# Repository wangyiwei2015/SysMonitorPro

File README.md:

# SysMonitor Pro 2.0

A hardware dashboard for your computer.

### Get started

1. Connect your device to a USB port
2. Launch the application and select its COM/Serial port
3. Done!

\* *To find the serial port on Windows, go to Device Manager.*

### Build

-> build_.bat

### To-do

The Python client will be replaced by:

- Windows: .NET app
- macOS: SwiftUI app

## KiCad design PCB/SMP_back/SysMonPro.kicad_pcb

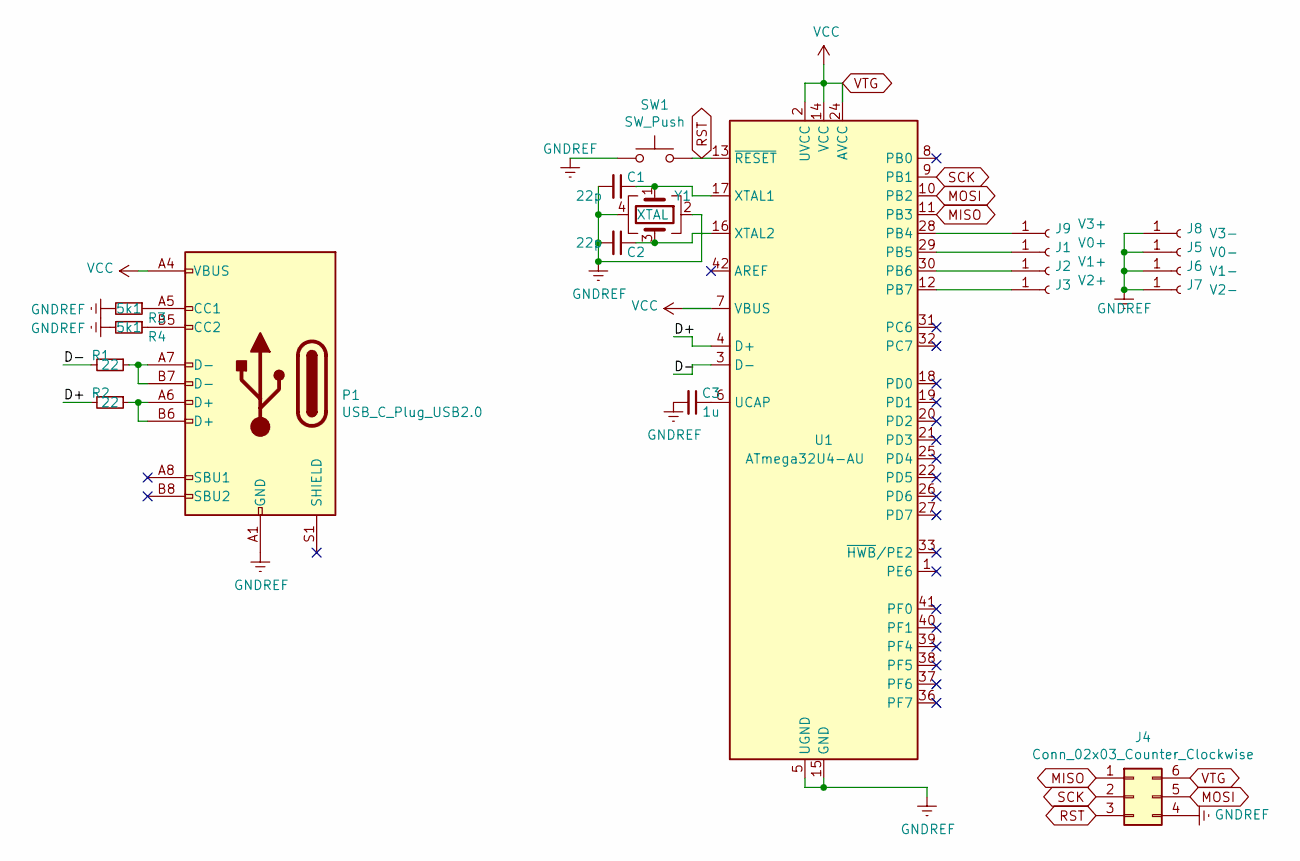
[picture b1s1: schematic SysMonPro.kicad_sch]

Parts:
C1, C2: 22p; C_0805_2012Metric_Pad1.18x1.45mm_HandSolder
C3: 1u; C_0805_2012Metric_Pad1.18x1.45mm_HandSolder
J1: V0+; MountingHole_4.3mm_M4_Pad_Via
J2: V1+; MountingHole_4.3mm_M4_Pad_Via
J3: V2+; MountingHole_4.3mm_M4_Pad_Via
J4: Conn_02x03_Counter_Clockwise; PinSocket_2x03_P2.54mm_Vertical
J5: V0-; MountingHole_4.3mm_M4_Pad_Via
J6: V1-; MountingHole_4.3mm_M4_Pad_Via
J7: V2-; MountingHole_4.3mm_M4_Pad_Via
J8: V3-; MountingHole_4.3mm_M4_Pad_Via
J9: V3+; MountingHole_4.3mm_M4_Pad_Via
P1: USB_C_Plug_USB2.0; USB_C_Receptacle_Palconn_UTC16-G
R1, R2: 22; R_0805_2012Metric_Pad1.20x1.40mm_HandSolder
R3, R4: 5k1; R_0805_2012Metric_Pad1.20x1.40mm_HandSolder
SW1: SW_Push; SW_SPST_SKQG_WithStem
U1: ATmega32U4-AU; TQFP-44_10x10mm_P0.8mm
Y1: XTAL; Crystal_SMD_3225-4Pin_3.2x2.5mm_HandSoldering

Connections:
/D+: R2.2, U1.4 (D+)
/D-: R1.2, U1.3 (D-)
GNDREF: C1.2, C2.2, C3.2, J4.4, J5.1, J6.1, J7.1, J8.1, P1.A1 (GND), P1.A12 (GND), P1.B1 (GND), P1.B12 (GND), R3.2, R4.2, SW1.1, U1.5 (UGND), U1.15 (GND), U1.23 (GND), U1.35 (GND), U1.43 (GND), Y1.2, Y1.4
MISO: J4.1, U1.11 (PB3)
MOSI: J4.5, U1.10 (PB2)
unnamed: C1.1, U1.17 (XTAL1), Y1.1
unnamed: C2.1, U1.16 (XTAL2), Y1.3
unnamed: C3.1, U1.6 (UCAP)
unnamed: J1.1, U1.29 (PB5)
unnamed: J2.1, U1.30 (PB6)
unnamed: J3.1, U1.12 (PB7)
unnamed: J9.1, U1.28 (PB4)
unnamed: P1.A5 (CC1), R3.1
unnamed: P1.A6 (D+), P1.B6 (D+), R2.1
unnamed: P1.A7 (D-), P1.B7 (D-), R1.1
unnamed: P1.B5 (CC2), R4.1
RST: J4.3, SW1.2, U1.13 (~RESET)
SCK: J4.2, U1.9 (PB1)
VTG: J4.6, P1.A4 (VBUS), P1.A9 (VBUS), P1.B4 (VBUS), P1.B9 (VBUS), U1.2 (UVCC), U1.7 (VBUS), U1.14 (VCC), U1.24 (AVCC), U1.34 (VCC), U1.44 (AVCC)

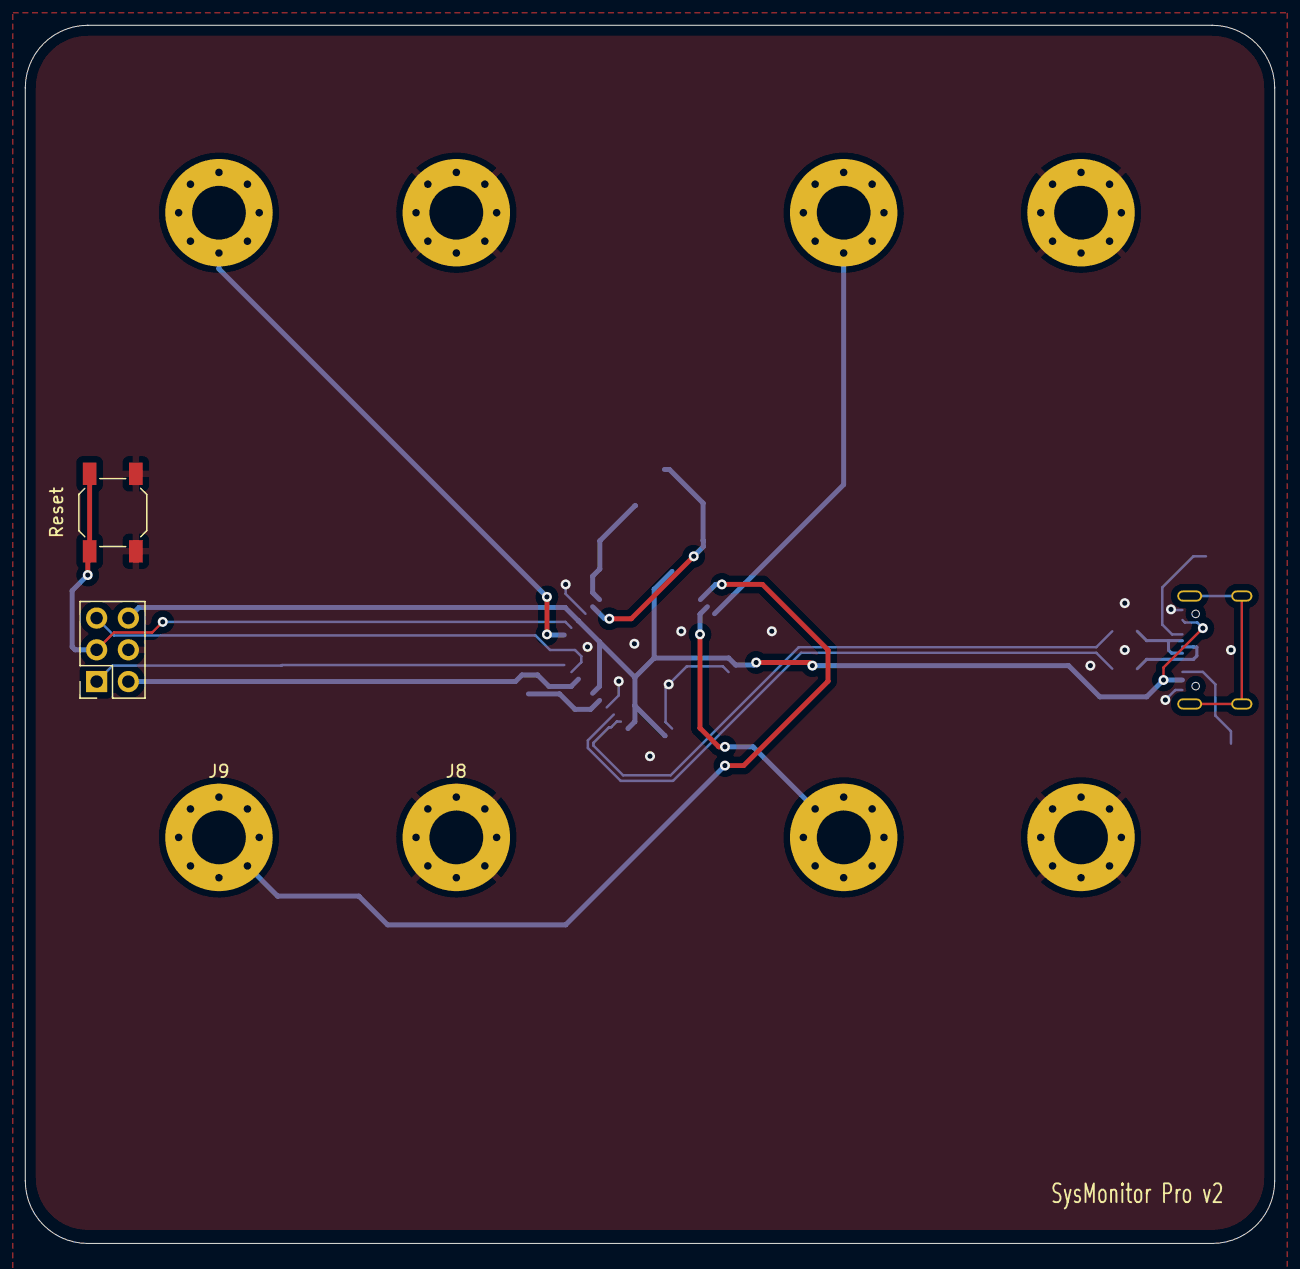
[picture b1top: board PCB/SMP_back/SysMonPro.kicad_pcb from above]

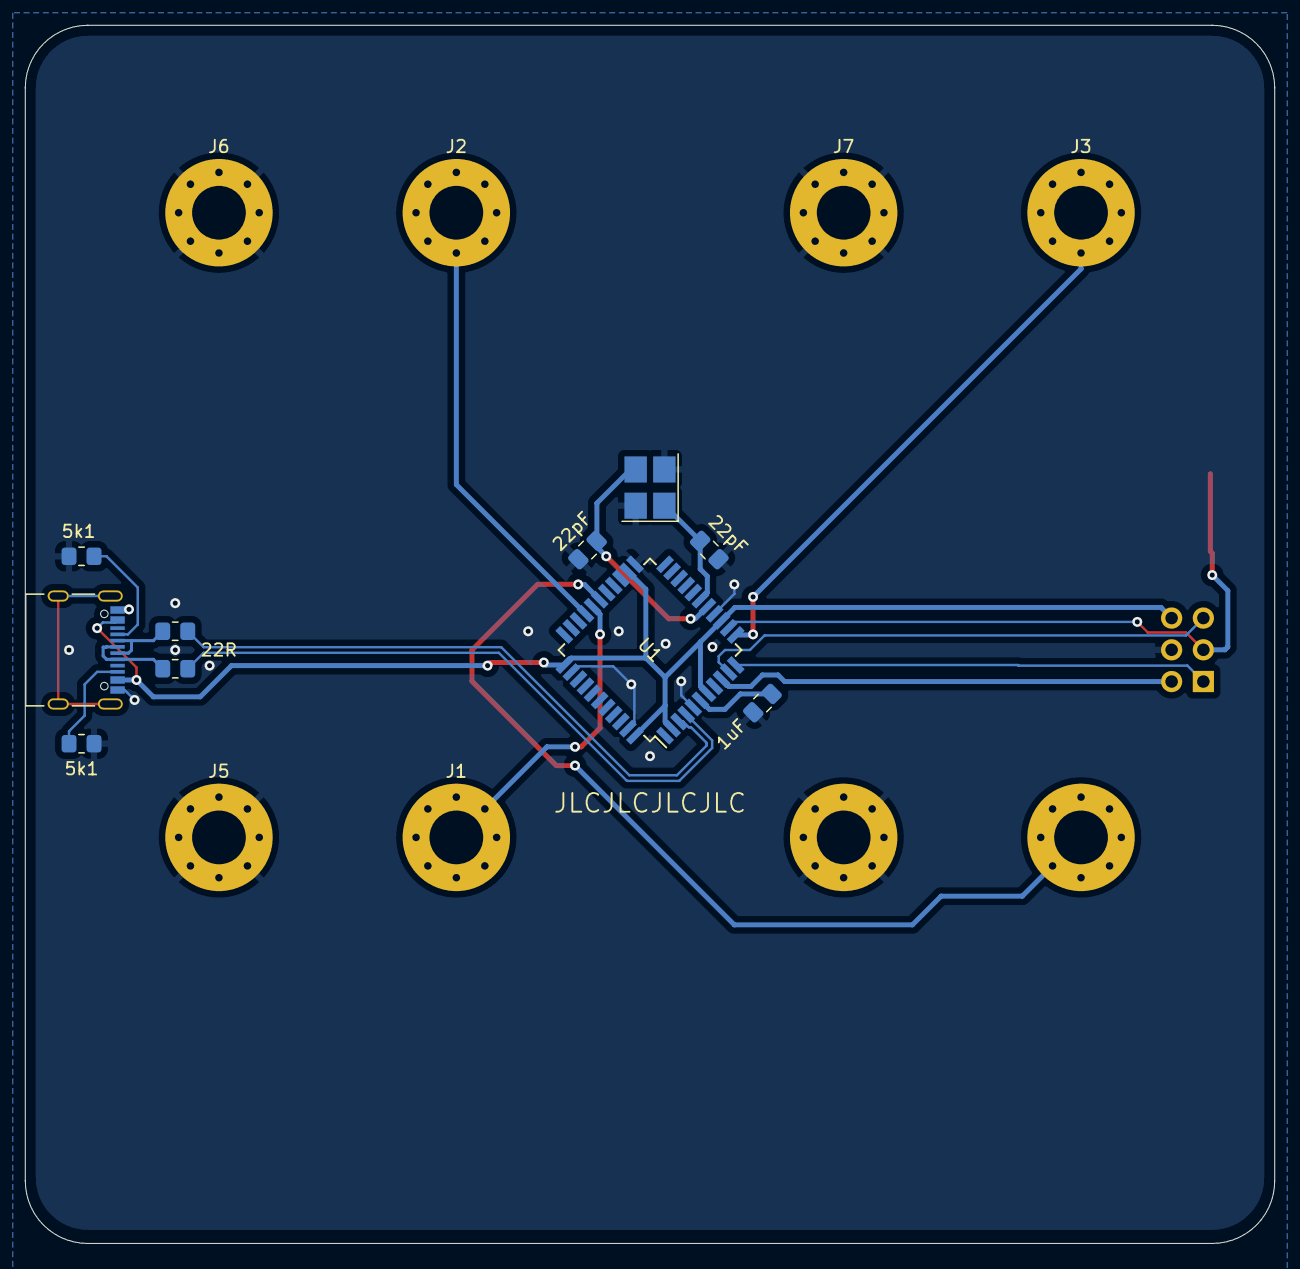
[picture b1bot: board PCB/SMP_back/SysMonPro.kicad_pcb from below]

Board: 2 copper layers, 100.0 x 97.5 mm, 20 parts (16 on the bottom side), 19 nets.

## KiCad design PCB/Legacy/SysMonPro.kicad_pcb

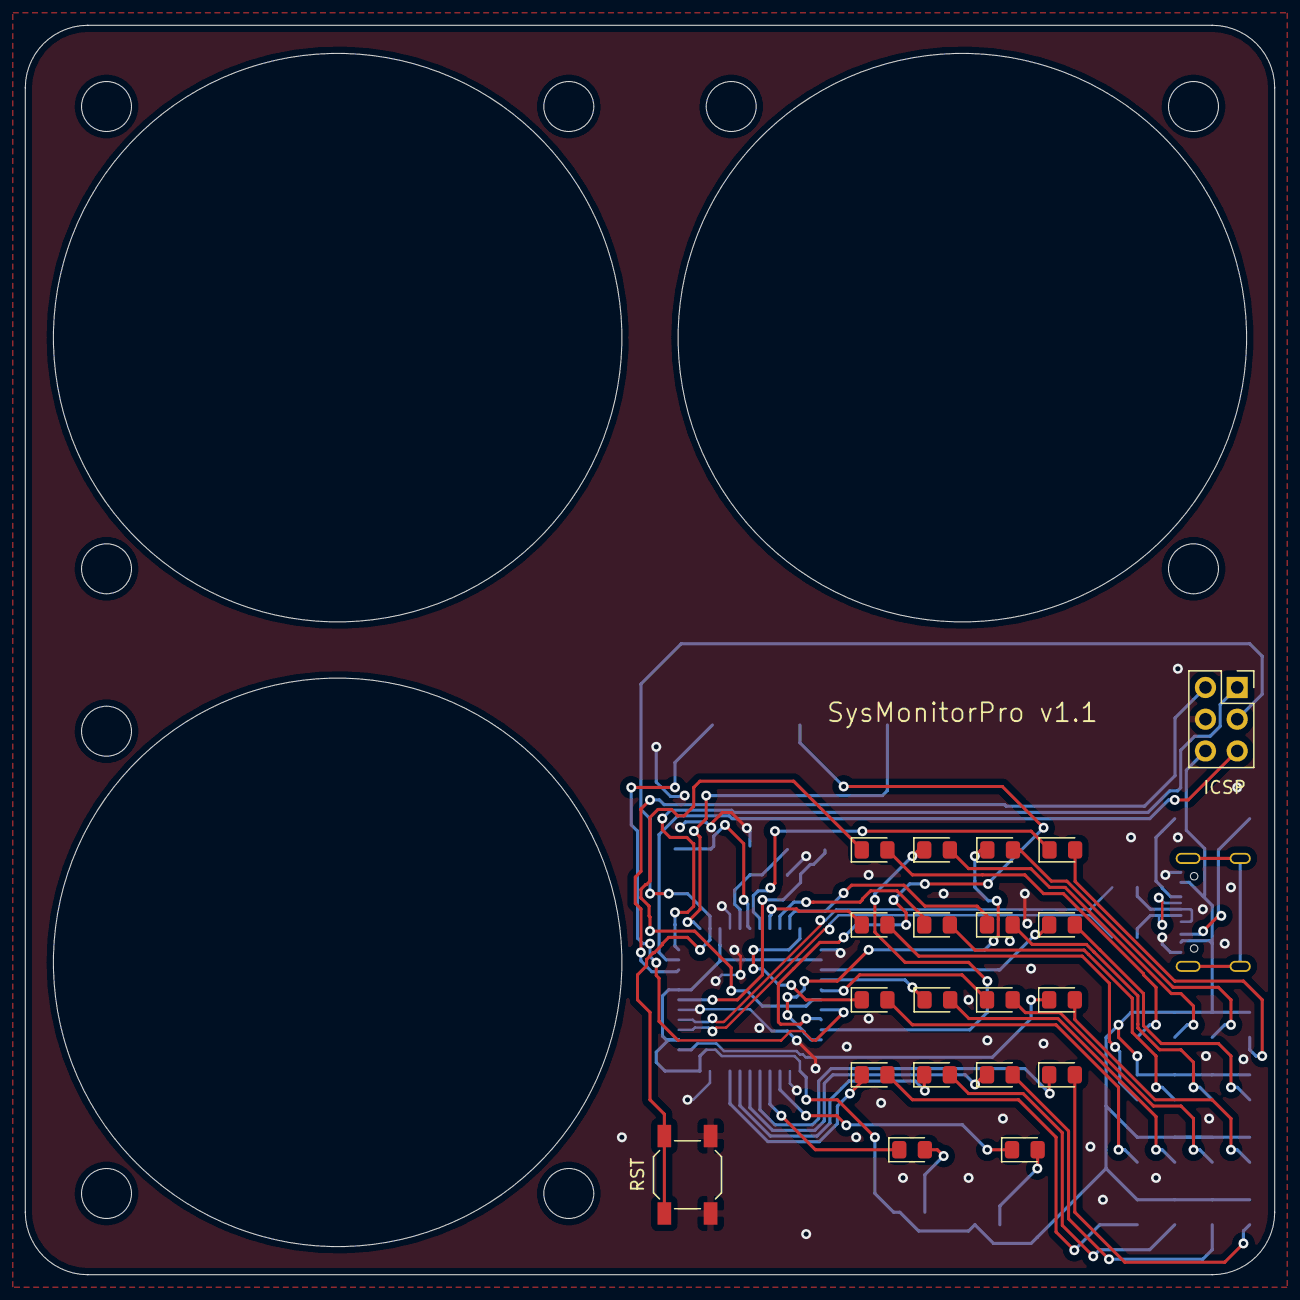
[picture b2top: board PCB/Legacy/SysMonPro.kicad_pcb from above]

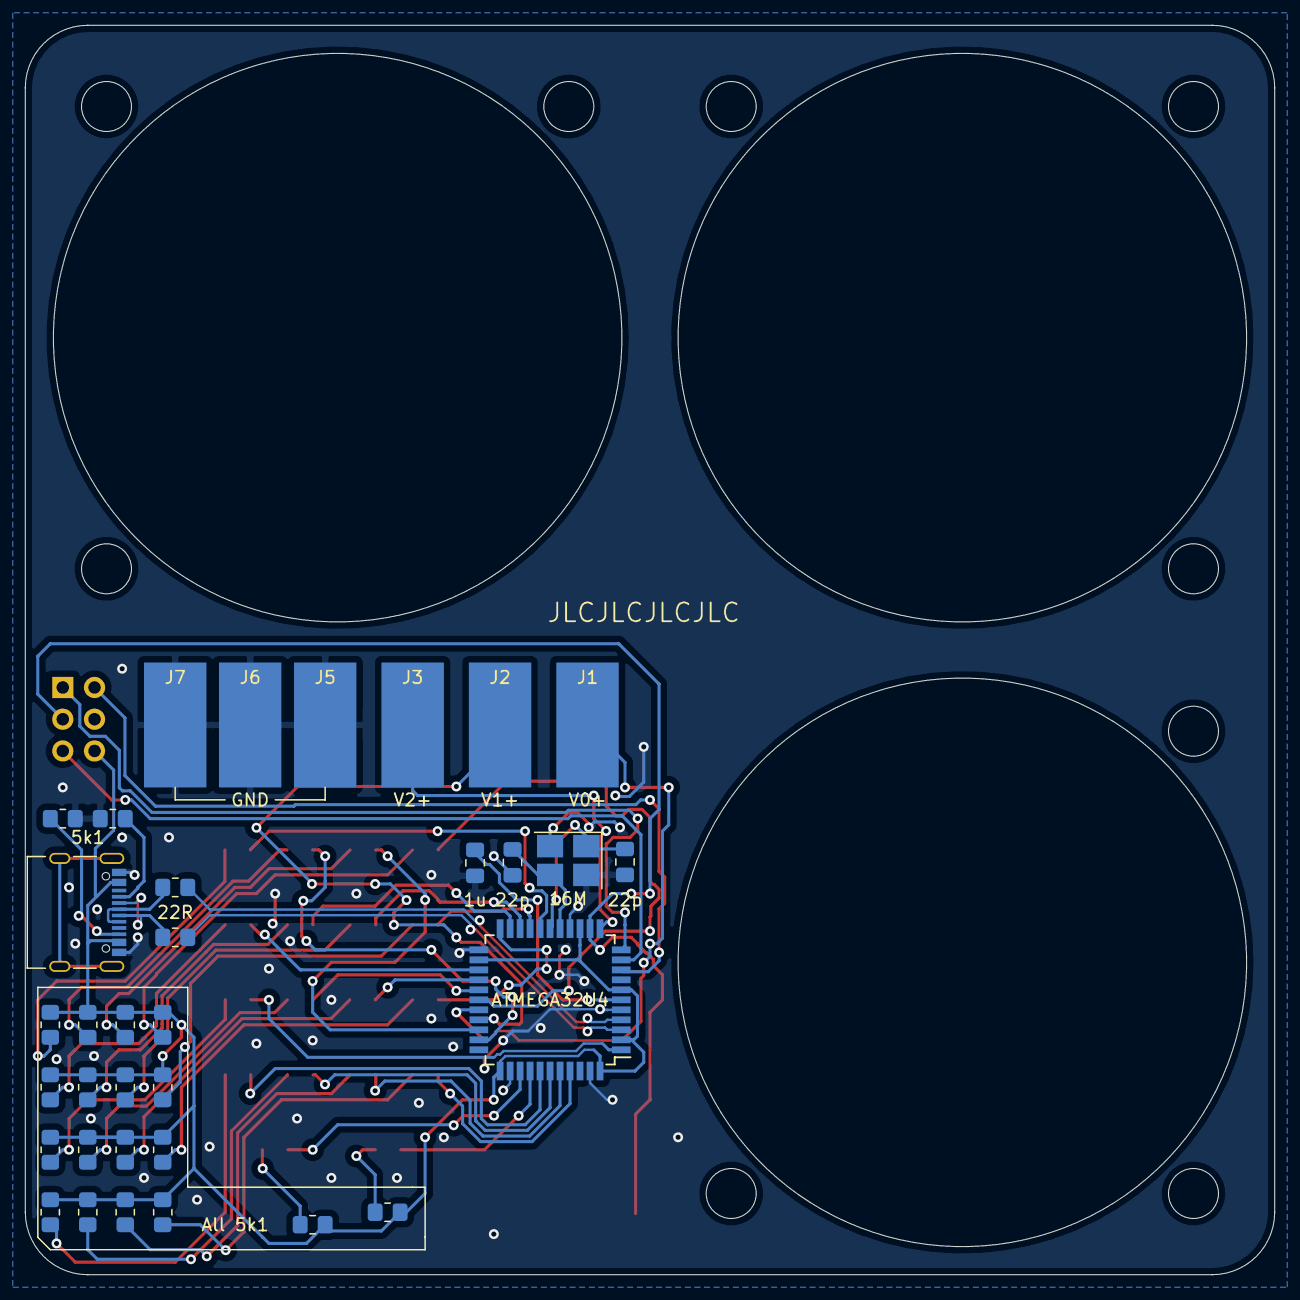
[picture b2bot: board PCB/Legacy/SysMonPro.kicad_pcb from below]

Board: 2 copper layers, 100.0 x 100.0 mm, 54 parts (34 on the bottom side), 54 nets.

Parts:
1u: 1u; C_0805_2012Metric_Pad1.18x1.45mm_HandSolder
5k1: 5k1; R_0805_2012Metric_Pad1.20x1.40mm_HandSolder
16M: XTAL; Crystal_SMD_3225-4Pin_3.2x2.5mm_HandSoldering
22R: 22; R_0805_2012Metric_Pad1.20x1.40mm_HandSolder
22p, 22p#2: 22p; C_0805_2012Metric_Pad1.18x1.45mm_HandSolder
ATMEGA32U4: ATmega32U4-AU; TQFP-44_10x10mm_P0.8mm
D1, D2, D3, D4, D5, D6, D7, D8, D9, D10, D11, D12, D13, D14, D15, D16, D17, D18: LED; D_0805_2012Metric_Pad1.15x1.40mm_HandSolder
ICSP: Conn_02x03_Counter_Clockwise; PinSocket_2x03_P2.54mm_Vertical
J1: V0+; SolderWirePad_1x01_SMD_5x10mm
J2: V1+; SolderWirePad_1x01_SMD_5x10mm
J3: V2+; SolderWirePad_1x01_SMD_5x10mm
J5: V0-; SolderWirePad_1x01_SMD_5x10mm
J6: V1-; SolderWirePad_1x01_SMD_5x10mm
J7: V2-; SolderWirePad_1x01_SMD_5x10mm
P1: USB_C_Plug_USB2.0; USB_C_Receptacle_Palconn_UTC16-G
R2: 22; R_0805_2012Metric_Pad1.20x1.40mm_HandSolder
R3: 5k1; R_0805_2012Metric_Pad1.20x1.40mm_HandSolder
R5, R6, R7, R8, R9, R10, R11, R12, R13, R14, R15, R16, R17, R18, R19, R20, R21, R22: 4k7; R_0805_2012Metric_Pad1.20x1.40mm_HandSolder
RST: SW_Push; SW_SPST_SKQG_WithStem

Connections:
/D+: ATMEGA32U4.4, R2.2
/D-: 22R.2, ATMEGA32U4.3
GNDREF: 1u.2, 5k1.2, 16M.2, 16M.4, 22p.2, 22p#2.2, ATMEGA32U4.5, ATMEGA32U4.15, ATMEGA32U4.23, ATMEGA32U4.35, ATMEGA32U4.43, ICSP.4, J5.1, J6.1, J7.1, P1.A1, P1.A12, P1.B1, P1.B12, R3.2, RST.1
MISO: ATMEGA32U4.11, ICSP.1
MOSI: ATMEGA32U4.10, ICSP.5
unnamed: 16M.1, 22p#2.1, ATMEGA32U4.17
unnamed: 16M.3, 22p.1, ATMEGA32U4.16
unnamed: 1u.1, ATMEGA32U4.6
unnamed: ATMEGA32U4.28, D1.1
unnamed: D1.2, R5.2
unnamed: ATMEGA32U4.31, D2.1
unnamed: D2.2, R6.2
unnamed: ATMEGA32U4.32, D3.1
unnamed: D3.2, R7.2
unnamed: ATMEGA32U4.18, D4.1
unnamed: D4.2, R8.2
unnamed: ATMEGA32U4.19, D5.1
unnamed: D5.2, R9.2
unnamed: ATMEGA32U4.20, D6.1
unnamed: D6.2, R10.2
unnamed: ATMEGA32U4.21, D7.1
unnamed: D7.2, R11.2
unnamed: ATMEGA32U4.25, D8.1
unnamed: D8.2, R12.2
unnamed: ATMEGA32U4.22, D9.1
unnamed: D9.2, R13.2
unnamed: ATMEGA32U4.26, D10.1
unnamed: D10.2, R14.2
unnamed: ATMEGA32U4.27, D11.1
unnamed: D11.2, R15.2
unnamed: ATMEGA32U4.1, D12.1
unnamed: D12.2, R16.2
unnamed: ATMEGA32U4.41, D13.1
unnamed: D13.2, R17.2
unnamed: ATMEGA32U4.40, D14.1
unnamed: D14.2, R18.2
unnamed: ATMEGA32U4.39, D15.1
unnamed: D15.2, R19.2
unnamed: ATMEGA32U4.38, D16.1
unnamed: D16.2, R20.2
unnamed: ATMEGA32U4.37, D17.1
unnamed: D17.2, R21.2
unnamed: ATMEGA32U4.36, D18.1
unnamed: D18.2, R22.2
unnamed: ATMEGA32U4.29, J1.1
unnamed: ATMEGA32U4.30, J2.1
unnamed: ATMEGA32U4.12, J3.1
unnamed: P1.A5, R3.1
unnamed: P1.A6, P1.B6, R2.1
unnamed: 22R.1, P1.A7, P1.B7
unnamed: 5k1.1, P1.B5
RST: ATMEGA32U4.13, ICSP.3, RST.2
SCK: ATMEGA32U4.9, ICSP.2
VTG: ATMEGA32U4.2, ATMEGA32U4.7, ATMEGA32U4.14, ATMEGA32U4.24, ATMEGA32U4.34, ATMEGA32U4.44, ICSP.6, P1.A4, P1.A9, P1.B4, P1.B9, R5.1, R6.1, R7.1, R8.1, R9.1, R10.1, R11.1, R12.1, R13.1, R14.1, R15.1, R16.1, R17.1, R18.1, R19.1, R20.1, R21.1, R22.1

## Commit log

2022-01-12 backup for 2.0
2022-05-29 updated v2 board
2022-07-05 enlarged hole
2023-05-23 backup
